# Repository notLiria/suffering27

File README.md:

# Suffering27
The suffering27 is fork of the Pain27, now featuring per-key leds and kailh hotswaps to use this as the macropad you never knew you needed

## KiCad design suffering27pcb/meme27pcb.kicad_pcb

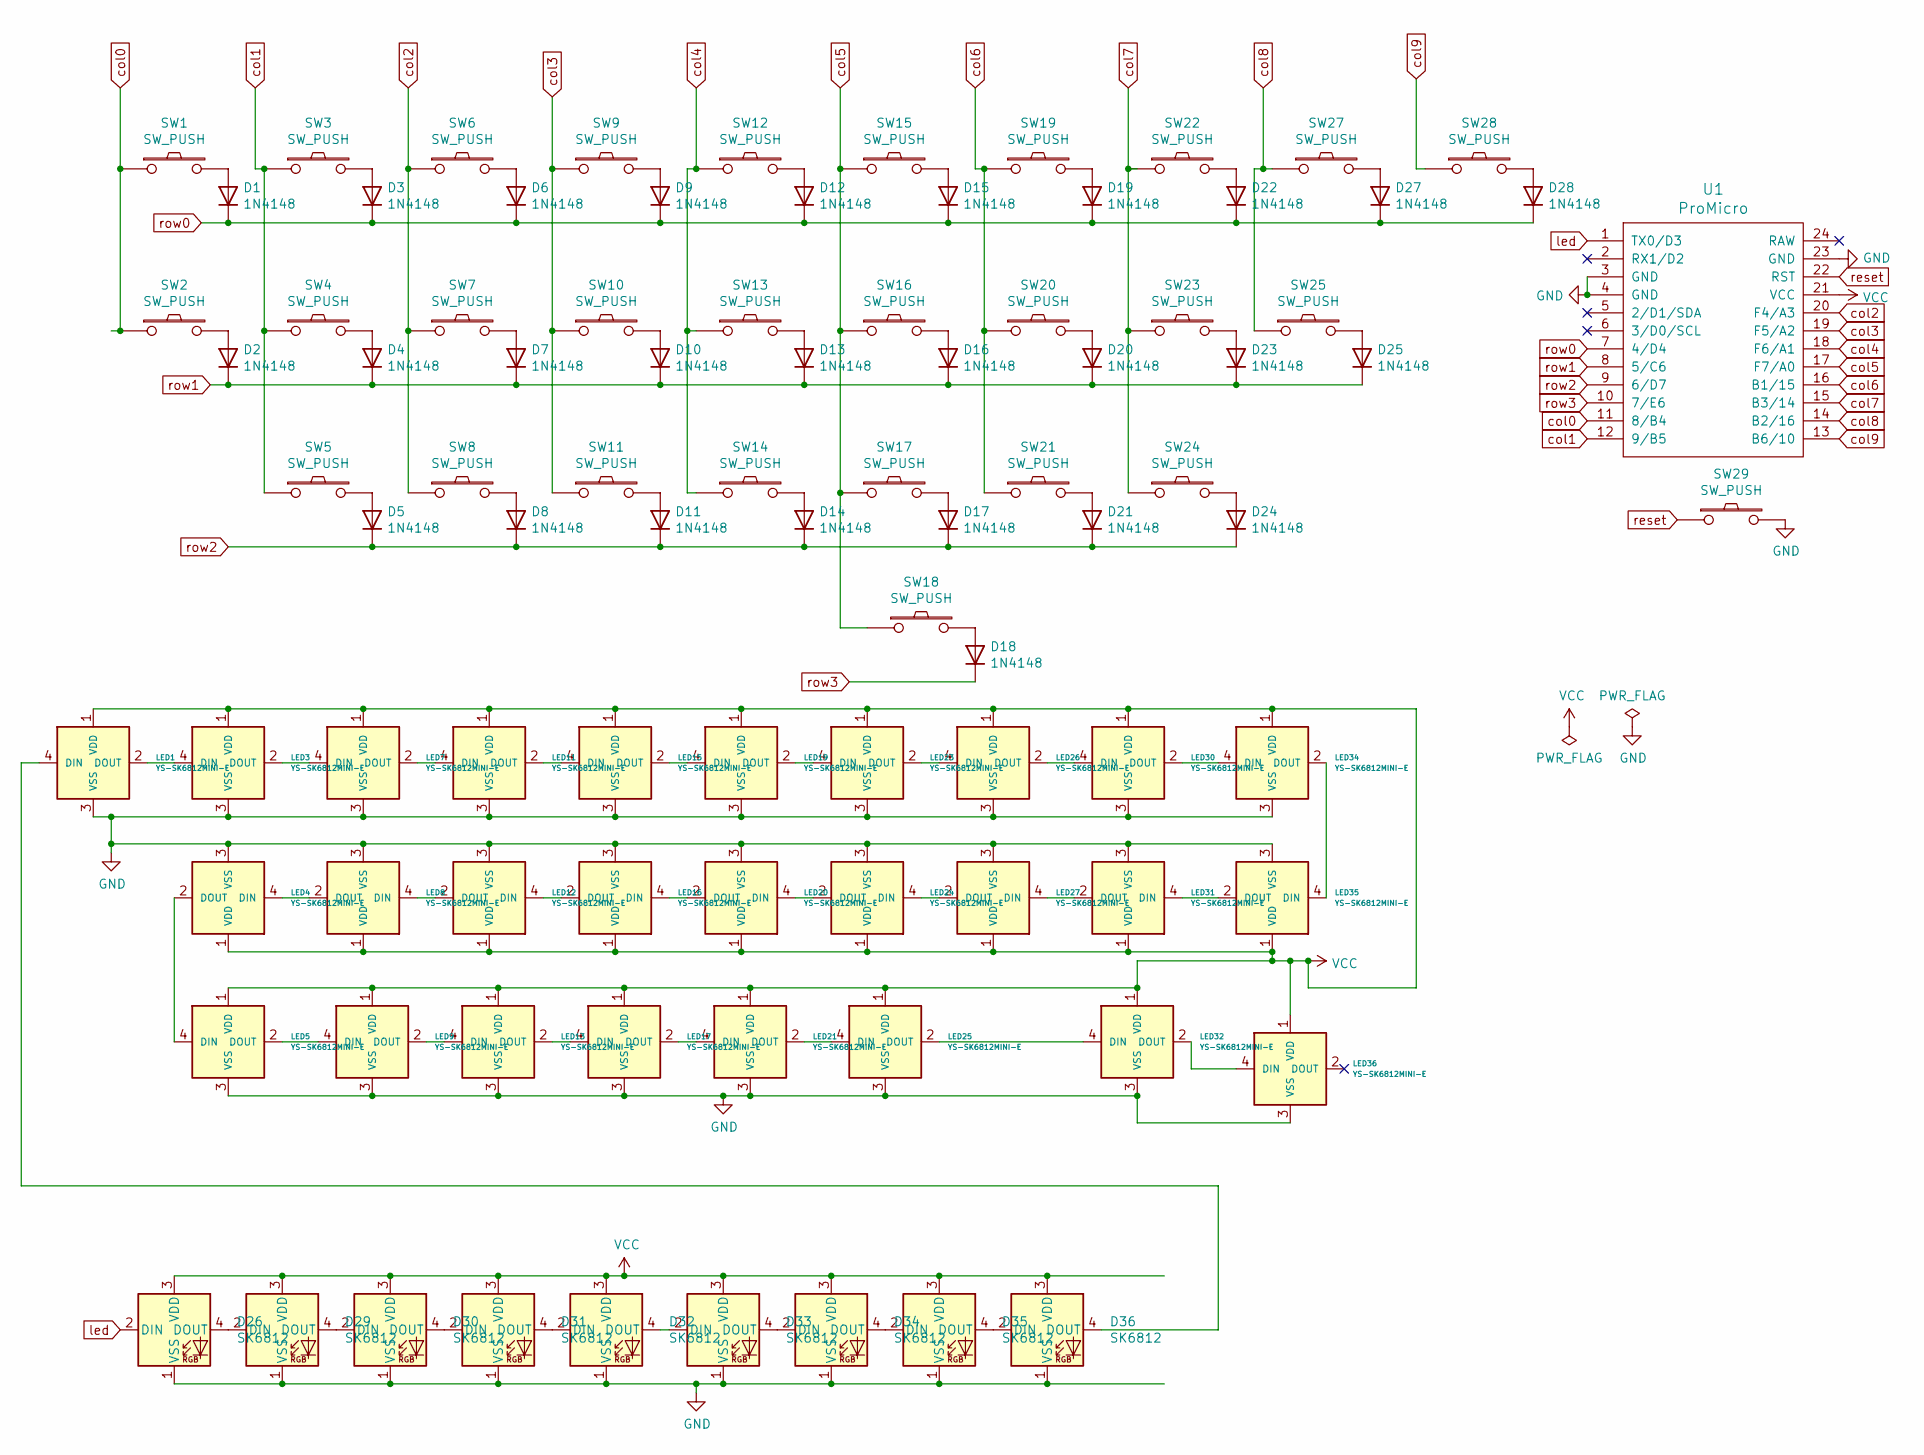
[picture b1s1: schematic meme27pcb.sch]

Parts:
D1, D2, D3, D4, D5, D6, D7, D8, D9, D10, D11, D12, D13, D14, D15, D16, D17, D18, D19, D20, D21, D22, D23, D24, D25, D27, D28: 1N4148; D3_SMD_v2
D26, D29, D30, D31, D32, D33, D34, D35, D36: SK6812; LED_WS2812B-PLCC4
LED1, LED3, LED4, LED5, LED7, LED8, LED9, LED11, LED12, LED13, LED15, LED16, LED17, LED19, LED20, LED21, LED23, LED24, LED25, LED26, LED27, LED30, LED31, LED32, LED34, LED35, LED36: YS-SK6812MINI-E
SW1, SW2, SW3, SW4, SW5, SW6, SW7, SW8, SW9, SW10, SW11, SW12, SW13, SW14, SW15, SW16, SW17, SW18, SW19, SW20, SW21, SW22, SW23, SW24, SW25, SW27, SW28: SW_PUSH; CherryMX_Hotswap
SW29: SW_PUSH; ResetSW_1side
U1: ProMicro; ProMicro_v3

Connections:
GND: D26.1 (VSS), D29.1 (VSS), D30.1 (VSS), D31.1 (VSS), D32.1 (VSS), D33.1 (VSS), D34.1 (VSS), D35.1 (VSS), D36.1 (VSS), LED1.3 (VSS), LED3.3 (VSS), LED4.3 (VSS), LED5.3 (VSS), LED7.3 (VSS), LED8.3 (VSS), LED9.3 (VSS), LED11.3 (VSS), LED12.3 (VSS), LED13.3 (VSS), LED15.3 (VSS), LED16.3 (VSS), LED17.3 (VSS), LED19.3 (VSS), LED20.3 (VSS), LED21.3 (VSS), LED23.3 (VSS), LED24.3 (VSS), LED25.3 (VSS), LED26.3 (VSS), LED27.3 (VSS), LED30.3 (VSS), LED31.3 (VSS), LED32.3 (VSS), LED34.3 (VSS), LED35.3 (VSS), LED36.3 (VSS), SW29.2, U1.3 (GND), U1.4 (GND), U1.23 (GND)
unnamed: D1.2 (A), SW1.2
unnamed: D2.2 (A), SW2.2
unnamed: D3.2 (A), SW3.2
unnamed: D4.2 (A), SW4.2
unnamed: D5.2 (A), SW5.2
unnamed: D6.2 (A), SW6.2
unnamed: D7.2 (A), SW7.2
unnamed: D8.2 (A), SW8.2
unnamed: D9.2 (A), SW9.2
unnamed: D10.2 (A), SW10.2
unnamed: D11.2 (A), SW11.2
unnamed: D12.2 (A), SW12.2
unnamed: D13.2 (A), SW13.2
unnamed: D14.2 (A), SW14.2
unnamed: D15.2 (A), SW15.2
unnamed: D16.2 (A), SW16.2
unnamed: D17.2 (A), SW17.2
unnamed: D18.2 (A), SW18.2
unnamed: D19.2 (A), SW19.2
unnamed: D20.2 (A), SW20.2
unnamed: D21.2 (A), SW21.2
unnamed: D22.2 (A), SW22.2
unnamed: D23.2 (A), SW23.2
unnamed: D24.2 (A), SW24.2
unnamed: D25.2 (A), SW25.2
unnamed: D26.4 (DOUT), D29.2 (DIN)
unnamed: D27.2 (A), SW27.2
unnamed: D28.2 (A), SW28.2
unnamed: D29.4 (DOUT), D30.2 (DIN)
unnamed: D30.4 (DOUT), D31.2 (DIN)
unnamed: D31.4 (DOUT), D32.2 (DIN)
unnamed: D32.4 (DOUT), D33.2 (DIN)
unnamed: D33.4 (DOUT), D34.2 (DIN)
unnamed: D34.4 (DOUT), D35.2 (DIN)
unnamed: D35.4 (DOUT), D36.2 (DIN)
unnamed: D36.4 (DOUT), LED1.4 (DIN)
unnamed: LED1.2 (DOUT), LED3.4 (DIN)
unnamed: LED3.2 (DOUT), LED7.4 (DIN)
unnamed: LED4.2 (DOUT), LED5.4 (DIN)
unnamed: LED4.4 (DIN), LED8.2 (DOUT)
unnamed: LED5.2 (DOUT), LED9.4 (DIN)
unnamed: LED11.2 (DOUT), LED15.4 (DIN)
unnamed: LED7.2 (DOUT), LED11.4 (DIN)
unnamed: LED8.4 (DIN), LED12.2 (DOUT)
unnamed: LED12.4 (DIN), LED16.2 (DOUT)
unnamed: LED13.2 (DOUT), LED17.4 (DIN)
unnamed: LED9.2 (DOUT), LED13.4 (DIN)
unnamed: LED15.2 (DOUT), LED19.4 (DIN)
unnamed: LED16.4 (DIN), LED20.2 (DOUT)
unnamed: LED17.2 (DOUT), LED21.4 (DIN)
unnamed: LED19.2 (DOUT), LED23.4 (DIN)
unnamed: LED20.4 (DIN), LED24.2 (DOUT)
unnamed: LED21.2 (DOUT), LED25.4 (DIN)
unnamed: LED23.2 (DOUT), LED26.4 (DIN)
unnamed: LED24.4 (DIN), LED27.2 (DOUT)
unnamed: LED25.2 (DOUT), LED32.4 (DIN)
unnamed: LED26.2 (DOUT), LED30.4 (DIN)
unnamed: LED27.4 (DIN), LED31.2 (DOUT)
unnamed: LED30.2 (DOUT), LED34.4 (DIN)
unnamed: LED31.4 (DIN), LED35.2 (DOUT)
unnamed: LED32.2 (DOUT), LED36.4 (DIN)
unnamed: LED34.2 (DOUT), LED35.4 (DIN)
VCC: D26.3 (VDD), D29.3 (VDD), D30.3 (VDD), D31.3 (VDD), D32.3 (VDD), D33.3 (VDD), D34.3 (VDD), D35.3 (VDD), D36.3 (VDD), LED1.1 (VDD), LED3.1 (VDD), LED4.1 (VDD), LED5.1 (VDD), LED7.1 (VDD), LED8.1 (VDD), LED9.1 (VDD), LED11.1 (VDD), LED12.1 (VDD), LED13.1 (VDD), LED15.1 (VDD), LED16.1 (VDD), LED17.1 (VDD), LED19.1 (VDD), LED20.1 (VDD), LED21.1 (VDD), LED23.1 (VDD), LED24.1 (VDD), LED25.1 (VDD), LED26.1 (VDD), LED27.1 (VDD), LED30.1 (VDD), LED31.1 (VDD), LED32.1 (VDD), LED34.1 (VDD), LED35.1 (VDD), LED36.1 (VDD), U1.21 (VCC)
col0: SW1.1, SW2.1, U1.11 (8/B4)
col1: SW3.1, SW4.1, SW5.1, U1.12 (9/B5)
col2: SW6.1, SW7.1, SW8.1, U1.20 (F4/A3)
col3: SW9.1, SW10.1, SW11.1, U1.19 (F5/A2)
col4: SW12.1, SW13.1, SW14.1, U1.18 (F6/A1)
col5: SW15.1, SW16.1, SW17.1, SW18.1, U1.17 (F7/A0)
col6: SW19.1, SW20.1, SW21.1, U1.16 (B1/15)
col7: SW22.1, SW23.1, SW24.1, U1.15 (B3/14)
col8: SW25.1, SW27.1, U1.14 (B2/16)
col9: SW28.1, U1.13 (B6/10)
led: D26.2 (DIN), U1.1 (TX0/D3)
reset: SW29.1, U1.22 (RST)
row0: D1.1 (K), D3.1 (K), D6.1 (K), D9.1 (K), D12.1 (K), D15.1 (K), D19.1 (K), D22.1 (K), D27.1 (K), D28.1 (K), U1.7 (4/D4)
row1: D2.1 (K), D4.1 (K), D7.1 (K), D10.1 (K), D13.1 (K), D16.1 (K), D20.1 (K), D23.1 (K), D25.1 (K), U1.8 (5/C6)
row2: D5.1 (K), D8.1 (K), D11.1 (K), D14.1 (K), D17.1 (K), D21.1 (K), D24.1 (K), U1.9 (6/D7)
row3: D18.1 (K), U1.10 (7/E6)

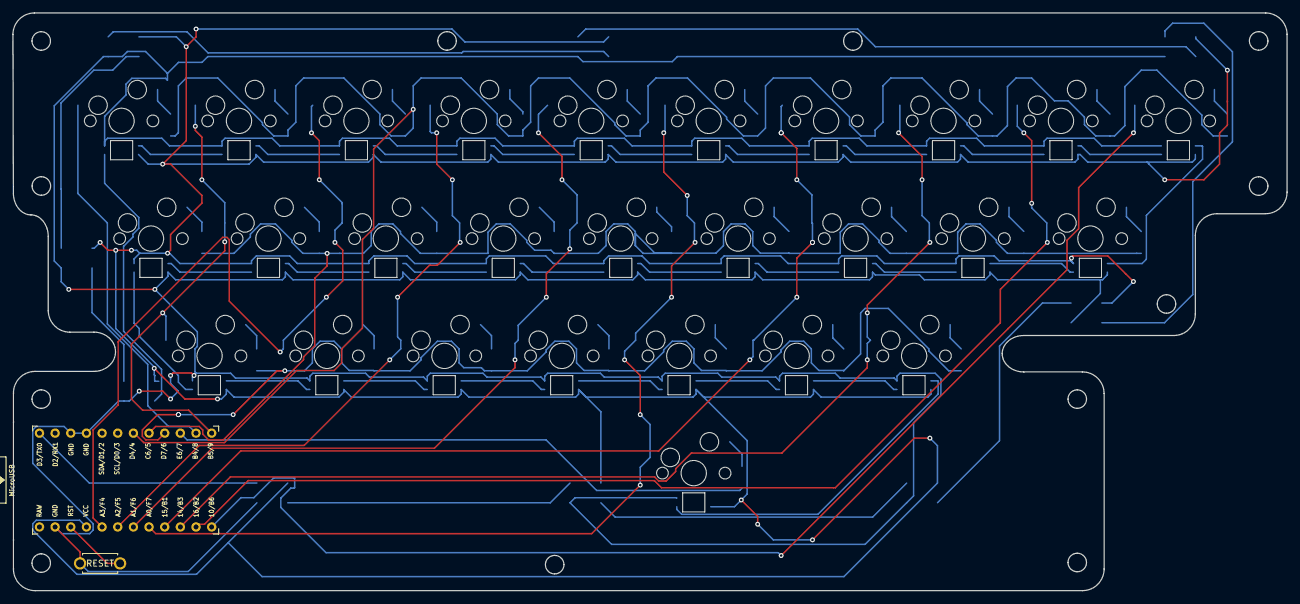
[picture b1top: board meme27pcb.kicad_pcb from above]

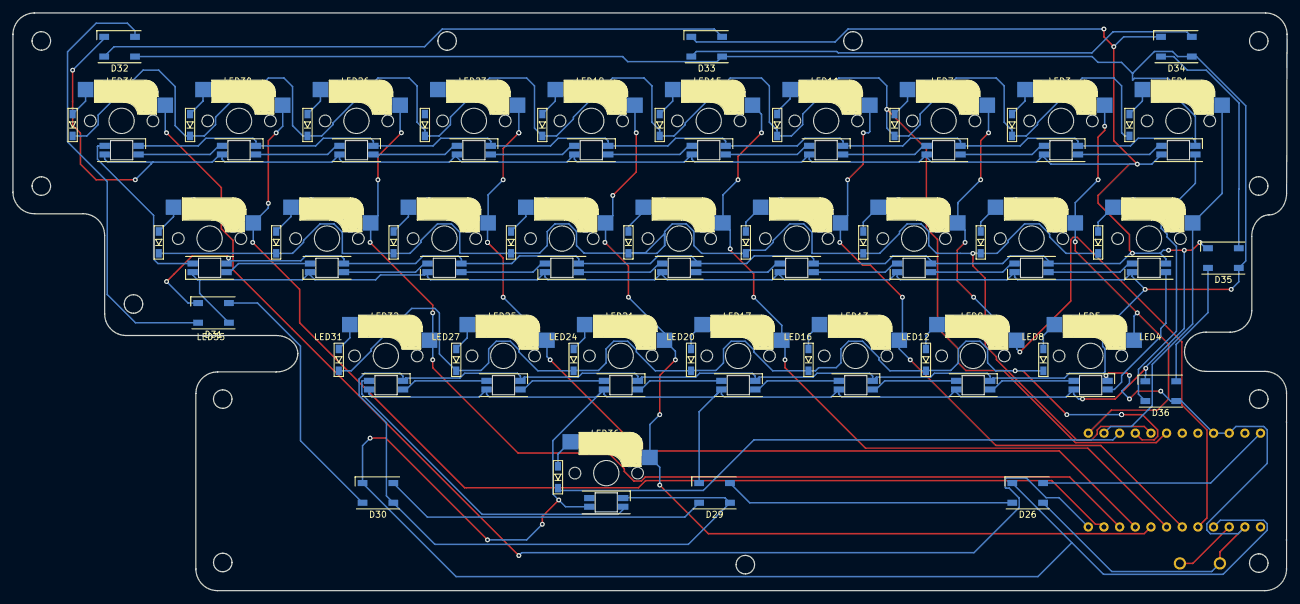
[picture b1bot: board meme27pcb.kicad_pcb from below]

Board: 2 copper layers, 206.7 x 93.7 mm, 92 parts (63 on the bottom side), 80 nets.
